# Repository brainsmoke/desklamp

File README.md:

# desk lamp

An attempt to try to build something, mostly from materials I already had on hand.

White LED lamp made with aluminium PCBs

|  |  |
|-|-|
|  |  |

# Serial commands (115200 baud)

```
$ screen /dev/ttyUSB1 115200

lampsh> help
commands:

blink
debug
factory reset
help
load blink [fade {0.00-60.00}]
load calibrations
load custom {0..3} [fade {0.00-60.00}]
load default [fade {0.00-60.00}]
off [fade {0.00-60.00}]
on [fade {0.00-60.00}]
print
reset
restore blink
restore calibrations
restore custom {0..3}
restore default
save blink
save calibrations
save custom {0..3}
save default
set gamma {1.0-5.5}
set led {0..8} ({0.00-100.00} | dial{0,1,2}[:{0.00-100.00}]) [fade {0.00-60.00}]
set leds ({0.00-100.00} | dial{0,1,2}[:{0.00-100.00}]) x 9 [fade {0.00-60.00}]
set max brightness {0.00-100.00}

```

## examples

```
lampsh> set max brightness 50.00               # set maximum brightness to 50%
lampsh> save                                   # make it permanent by saving it to eeprom
```

```
lampsh> set led 2 dial2:50.00                  # use dial2 to dim led 2 in the range 0%-50%

lampsh> set leds dial0 0 0 0 dial1 0 0 0 dial2 # drive one led/dial, each a different temp & pcb

lampsh> set leds dial0 dial1 dial2 dial0 dial1 dial2 dial0 dial1 dial2 # default setting
```

# Firmware

```
apt install avr-gcc gmake pip3
pip3 install pymcuprog
cd firmware/attiny1624
make
make flash

```

# LED brightness calculation

```

    per LED                                      interpolate       apply     scale
     config                                      transition        gamma   brightness
 --------------                                 -------------     -------  ----------
                                                                              max 
 current config                                t_cur / interval    gamma   brightness
                                                     |               |         |
 .-------------.                                     V               V         |
 | per LED     |               .---.         .---------------.  .--------.     |
 | brightness  |---------------- * --------->|          .__  |  |        |     V
 |_____________|               '-^-'         |        ."     |  |       '|   .---.
                                 |           |       /       |->|      / |-->| * |
 .-------------.           .------------. .->|      /        |  |     /  |   '---'
 | per LED     |-dial 0-2->| dial value | |  |  __-'         |  | __-'   |     |
 | dial select |           |------------| |  '_______________'  '________'     |
 |_____________|-no dial-->| max        | |  |               |                 V
                           |____________| |  | sigmoid       |          .------------.
 previous config                          |  | interpolation |          |    LED     |
                                          |  |_______________|          | brightness |
 .-------------.                          |                             '------------'
 | per LED     |               .---.      |
 | brightness  |---------------- * -------'
 |_____________|               '-^-'
                                 |
 .-------------.           .------------.
 | per LED     |-dial 0-2->| dial value |
 | dial select |           |------------|
 |_____________|-no dial-->| max        |
                           |____________|
                           
```

# LED PCBs are leftovers from:

https://github.com/brainsmoke/aluball

## PADAUK software:

https://github.com/brainsmoke/softpwmpdk

`./write.sh <address>` for each in 0..2

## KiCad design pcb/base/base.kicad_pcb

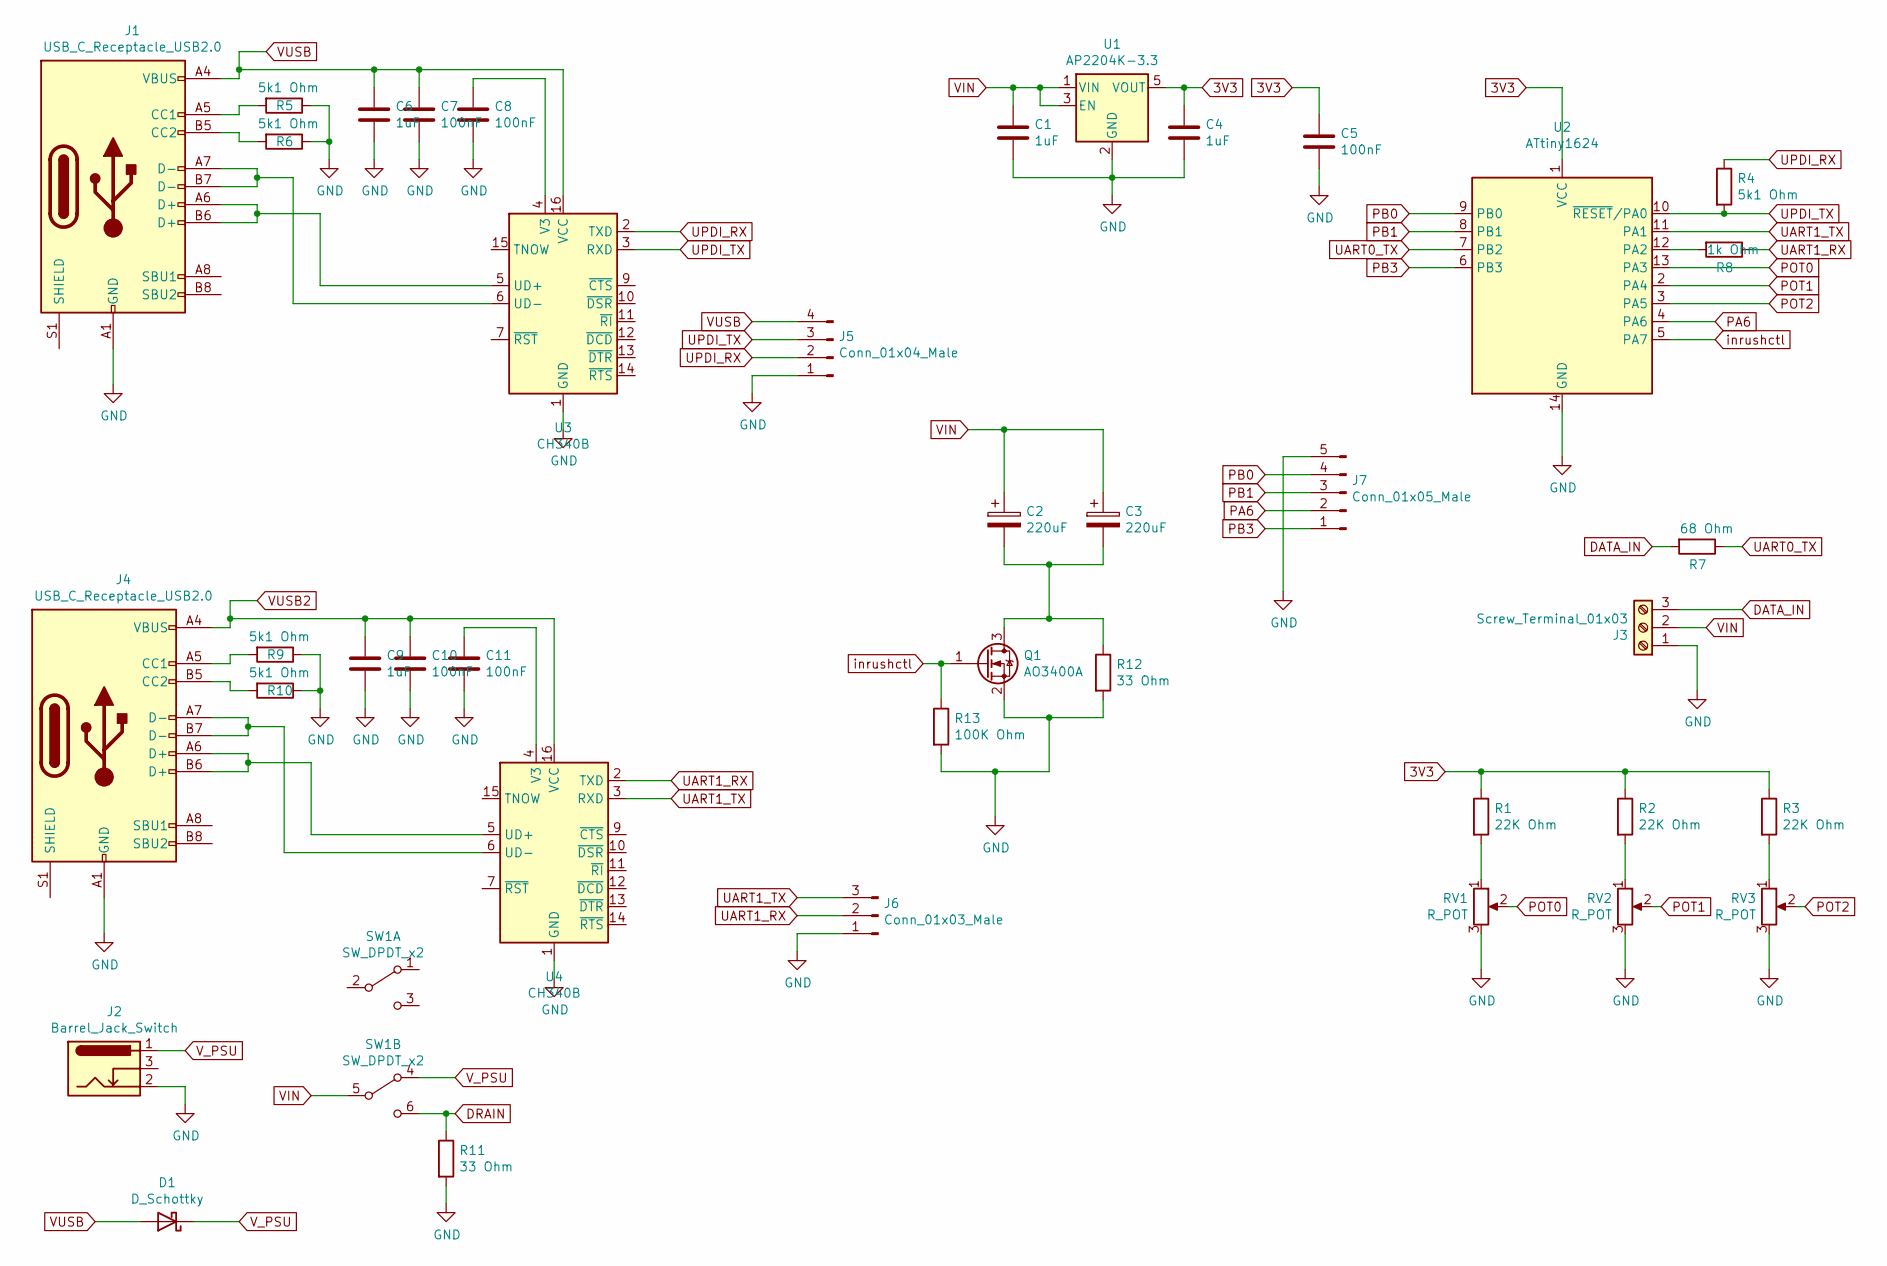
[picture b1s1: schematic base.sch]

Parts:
C1, C4, C6, C9: 1uF; C_0603_1608Metric_Pad1.08x0.95mm_HandSolder
C2, C3: 220uF; CP_Elec_10x10
C5, C7, C8, C10, C11: 100nF; C_0603_1608Metric_Pad1.08x0.95mm_HandSolder
D1: D_Schottky; D_SOD-123
J1, J4: USB_C_Receptacle_USB2.0; USB_C_Receptacle_HRO_TYPE-C-31-M-12
J2: Barrel_Jack_Switch; BarrelJack_Horizontal
J3: Screw_Terminal_01x03; TerminalBlock_Phoenix_PT-1,5-3-5.0-H_1x03_P5.00mm_Horizontal
J5: Conn_01x04_Male; PinHeader_1x04_P2.54mm_Vertical
J6: Conn_01x03_Male; PinHeader_1x03_P2.54mm_Vertical
J7: Conn_01x05_Male; PinHeader_1x05_P2.54mm_Vertical
Q1: AO3400A; SOT-23
R1, R2, R3: 22K Ohm; R_0603_1608Metric_Pad0.98x0.95mm_HandSolder
R4, R5, R6, R9, R10: 5k1 Ohm; R_0603_1608Metric_Pad0.98x0.95mm_HandSolder
R7: 68 Ohm; R_0603_1608Metric_Pad0.98x0.95mm_HandSolder
R8: 1k Ohm; R_0603_1608Metric_Pad0.98x0.95mm_HandSolder
R11, R12: 33 Ohm; R_1206_3216Metric_Pad1.30x1.75mm_HandSolder
R13: 100K Ohm; R_0603_1608Metric_Pad0.98x0.95mm_HandSolder
RV1, RV2, RV3: R_POT; Potentiometer_Alps_RK09L_Single_Vertical_radial
SW1: SW_DPDT_x2; MTS-20X_DPDT
U1: AP2204K-3.3; SOT-23-5
U2: ATtiny1624; SOIC-14_3.9x8.7mm_P1.27mm
U3, U4: CH340B; SOIC-16_3.9x9.9mm_P1.27mm

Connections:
3V3: C4.1, C5.1, R1.1, R2.1, R3.1, U1.5 (VOUT), U2.1 (VCC)
DATA_IN: J3.3, R7.2
DRAIN: R11.1, SW1.6 (C)
GND: C1.2, C4.2, C5.2, C6.2, C7.2, C8.2, C9.2, C10.2, C11.2, J1.A1 (GND), J1.A12 (GND), J1.B1 (GND), J1.B12 (GND), J2.2, J3.1, J4.A1 (GND), J4.A12 (GND), J4.B1 (GND), J4.B12 (GND), J5.1, J6.1, J7.5, Q1.2 (S), R5.1, R6.1, R9.1, R10.1, R11.2, R12.2, R13.2, RV1.3, RV2.3, RV3.3, U1.2 (GND), U2.14 (GND), U3.1 (GND), U4.1 (GND)
unnamed: C2.2, C3.2, Q1.3 (D), R12.1
unnamed: C8.1, U3.4 (V3)
unnamed: C11.1, U4.4 (V3)
unnamed: J1.A5 (CC1), R5.2
unnamed: J1.A6 (D+), J1.B6 (D+), U3.5 (UD+)
unnamed: J1.A7 (D-), J1.B7 (D-), U3.6 (UD-)
unnamed: J1.B5 (CC2), R6.2
unnamed: J4.A5 (CC1), R9.2
unnamed: J4.A6 (D+), J4.B6 (D+), U4.5 (UD+)
unnamed: J4.A7 (D-), J4.B7 (D-), U4.6 (UD-)
unnamed: J4.B5 (CC2), R10.2
unnamed: R1.2, RV1.1
unnamed: R2.2, RV2.1
unnamed: R3.2, RV3.1
unnamed: R8.2, U2.12 (PA2)
PA6: J7.2, U2.4 (PA6)
PB0: J7.4, U2.9 (PB0)
PB1: J7.3, U2.8 (PB1)
PB3: J7.1, U2.6 (PB3)
POT0: RV1.2, U2.13 (PA3)
POT1: RV2.2, U2.2 (PA4)
POT2: RV3.2, U2.3 (PA5)
UART0_TX: R7.1, U2.7 (PB2)
UART1_RX: J6.2, R8.1, U4.2 (TXD)
UART1_TX: J6.3, U2.11 (PA1), U4.3 (RXD)
UPDI_RX: J5.2, R4.1, U3.2 (TXD)
UPDI_TX: J5.3, R4.2, U2.10 (~RESET~/PA0), U3.3 (RXD)
VIN: C1.1, C2.1, C3.1, J3.2, SW1.5 (B), U1.1 (VIN), U1.3 (EN)
VUSB: C6.1, C7.1, D1.2 (A), J1.A4 (VBUS), J1.A9 (VBUS), J1.B4 (VBUS), J1.B9 (VBUS), J5.4, U3.16 (VCC)
VUSB2: C9.1, C10.1, J4.A4 (VBUS), J4.A9 (VBUS), J4.B4 (VBUS), J4.B9 (VBUS), U4.16 (VCC)
V_PSU: D1.1 (K), J2.1, SW1.4 (A)
inrushctl: Q1.1 (G), R13.1, U2.5 (PA7)

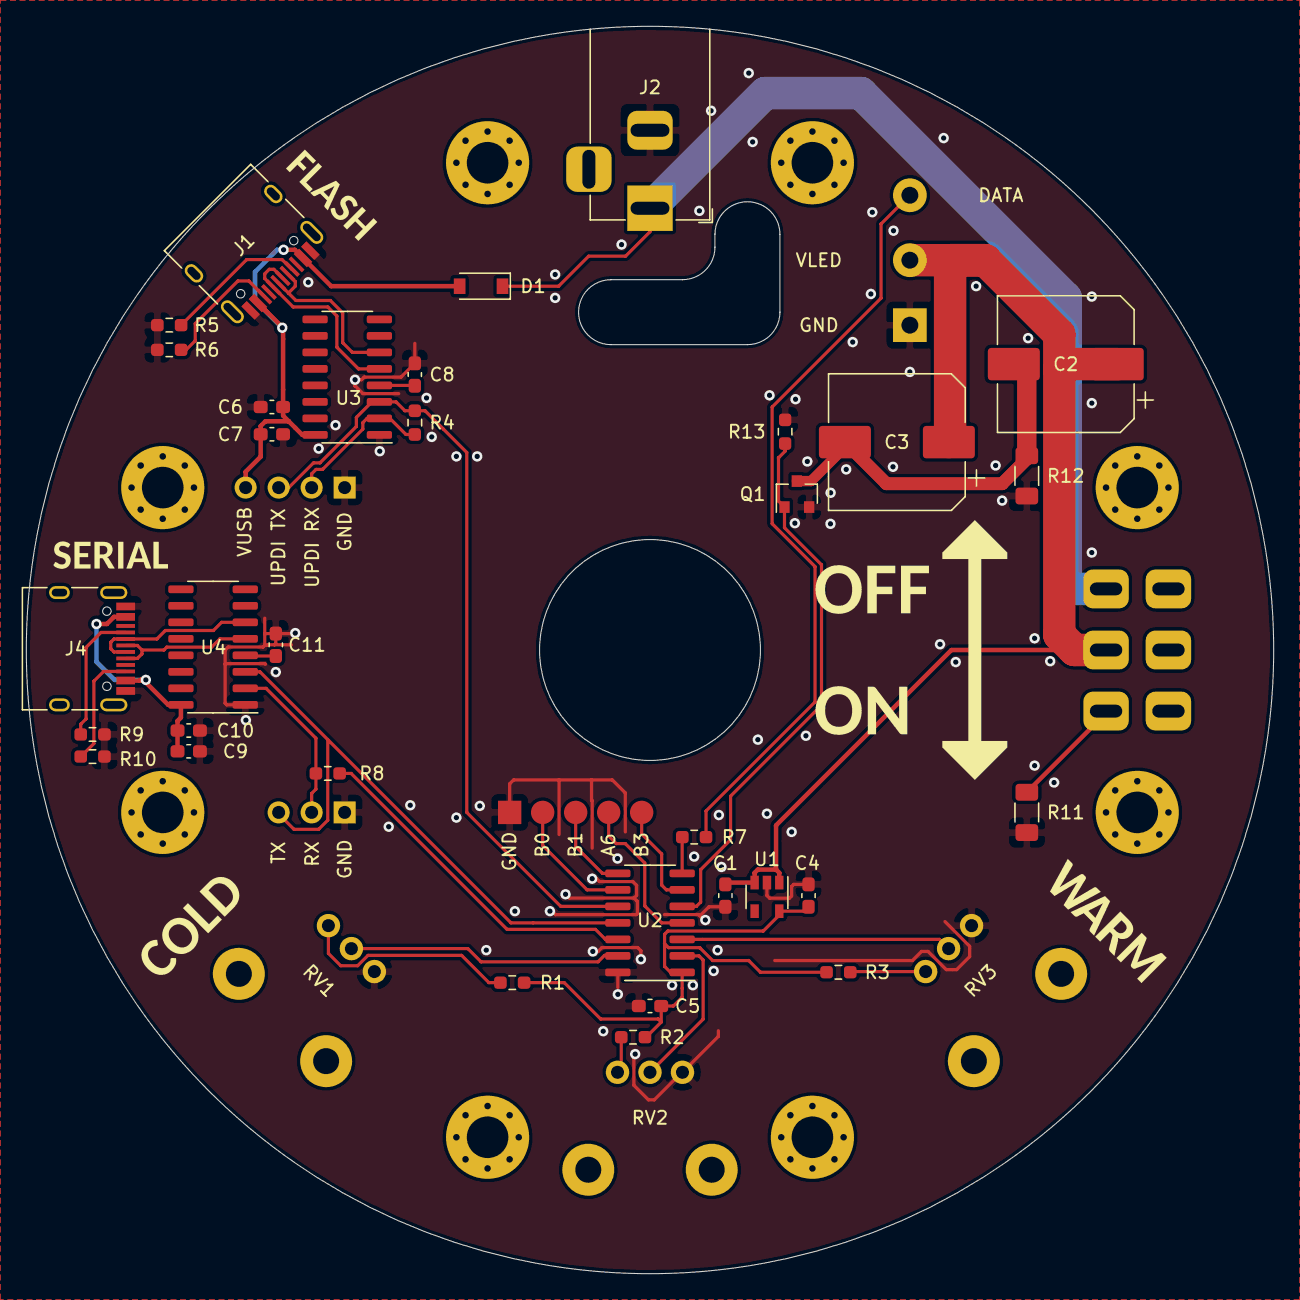
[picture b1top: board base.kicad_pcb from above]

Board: 2 copper layers, 96.0 x 96.0 mm, 41 parts (0 on the bottom side), 36 nets.

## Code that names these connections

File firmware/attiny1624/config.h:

#ifndef CONFIG_H
#define CONFIG_H

#define F_CPU 10000000UL
#define F_CPU_BITS (CLKCTRL_PEN_bm) /* has to match with the bits for F_CPU */

#define EEPROM_MAGIC (0x504d414c)

#define N_DIALS       3
#define DIAL_WHITE             0
#define DIAL_WARM_WHITE        1
#define DIAL_EXTRA_WARM_WHITE  2
#define NO_DIAL                3
#define STR_DIAL_RANGE        "dial{0,1,2}"


#define N_LEDS         9
#define STR_N_LEDS    "9"
#define STR_LED_RANGE "{0..8}"

#define STR_BRIGHTNESS_RANGE "{0.00-100.00}"

#define DEFAULT_FADE (60)
#define STR_FADE_RANGE "{0.00-60.00}"
#define FADE_MAX (6000)

#define STR_GAMMA_RANGE "{1.0-5.5}"

#define LED_ALL_OFF 0,0,0, 0,0,0, 0,0,0
#define LED_ALL_MAX 0xffff, 0xffff, 0xffff, 0xffff, 0xffff, 0xffff, 0xffff, 0xffff, 0xffff

#define LED_BLINK 0xffff, 0, 0, 0xffff, 0, 0, 0xffff, 0, 0

#define LED_ORDER DIAL_WHITE, DIAL_WARM_WHITE, DIAL_EXTRA_WARM_WHITE

#define LED_DIAL_MAP       LED_ORDER, LED_ORDER, LED_ORDER
#define LED_NO_DIAL_MAP NO_DIAL,NO_DIAL,NO_DIAL, NO_DIAL,NO_DIAL,NO_DIAL, NO_DIAL,NO_DIAL,NO_DIAL

#define LED_UART_RESHUFFLE 0,2,1,3,5,4,6,8,7

#define ANIMATION_QUEUE_SIZE 16

#define N_CUSTOM            4
#define N_PRESETS           6
#define PRESET_CUSTOM_BASE  0
#define PRESET_DEFAULT      4
#define PRESET_BLINK        5
#define STR_CUSTOM_RANGE "{0..3}"
#define PRESET_NAMES "custom 0", "custom 1", "custom 2", "custom 3", "default", "blink"

#define DIAL_MIN_DEFAULT 600
#define DIAL_MAX_DEFAULT 60000
#define DIAL_DEADZONE 400        /* full-on / full-off regions */

#define DEFAULT_MAX_BRIGHTNESS (65535)
#define DEFAULT_GAMMA_DEC (20) /* gamma = gamma_dec/10 */

#define ADC_PIN_0     3
#define ADC_PORT_0    PORTA
#define ADC_PINCTRL_0 PORTA.PIN3CTRL
#define ADC_AIN_0     3

#define ADC_PIN_1     4
#define ADC_PORT_1    PORTA
#define ADC_PINCTRL_1 PORTA.PIN4CTRL
#define ADC_AIN_1     4

#define ADC_PIN_2     5
#define ADC_PORT_2    PORTA
#define ADC_PINCTRL_2 PORTA.PIN5CTRL
#define ADC_AIN_2     5

#define USART0_BAUDRATE 38400
#define USART1_BAUDRATE 115200

#define USART0_RX_BUF_SZ (1)
#define USART1_RX_BUF_SZ (254)


#define USART0_PORTMUX PORTMUX_USART0_DEFAULT_gc // RX = PB3, TX = PB2
#define USART0_BAUD_REG ( (F_CPU*64 + 8ul*USART0_BAUDRATE)/(16ul*USART0_BAUDRATE) )

#define USART1_PORTMUX PORTMUX_USART1_DEFAULT_gc // RX = PA2, TX = PA1
#define USART1_BAUD_REG ( (F_CPU*64 + 8ul*USART1_BAUDRATE)/(16ul*USART1_BAUDRATE) )

#define USART0_RX_PIN 3
#define USART0_RX_PORT PORTB
#define USART0_RX_PINCTRL PORTB.PIN3CTRL

#define USART0_TX_PIN 2
#define USART0_TX_PORT PORTB
#define USART0_TX_PINCTRL PORTB.PIN2CTRL

#define USART1_RX_PIN 2
#define USART1_RX_PORT PORTA
#define USART1_RX_PINCTRL PORTA.PIN2CTRL

#define USART1_TX_PIN 1
#define USART1_TX_PORT PORTA
#define USART1_TX_PINCTRL PORTA.PIN1CTRL

#endif //CONFIG_H

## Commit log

2023-04-08 pcb ok, code untested
2023-04-08 debug some stuff
2023-04-09 add gamma config
2023-04-09 fix dial to colour mapping
2023-04-10 remove inv parameter in output
2023-04-10 add rtc leap calculator
2023-04-13 use yield() for polling
2023-04-14 readme
2023-04-14 add smooth transitions
2023-04-14 add PCB image
2023-04-15 copy animation presets by value in animation queue
2023-04-15 add led preset config parser function
2023-04-15 allow setting leds over serial
2023-04-15 rename dial[1..3] to dial[0..2] for consistency
2023-04-15 well.. oops
2023-04-15 improve command parsing, add help command
2023-04-15 add commands to readme
2023-04-16 wut!?
2023-04-16 fix crlf handling
2023-04-16 use percentages for brightness
2023-04-16 clarify documentation
2023-04-16 firmware build doc
2023-04-17 optimise interpolation stuff
2023-04-18 save the bytes! reuse code
2023-04-18 rename config => dial member in preset_t
2023-04-18 add drain resistor to pcb
2023-04-18 rename preset_t to ledconfig_t
2023-04-19 add configurable presets
2023-04-19 add uart header
2023-04-19 remove unused header
2023-04-19 change {load,save} commands to {load,save,restore} calibrations
2023-04-19 simplefy code
2023-04-19 fix arg parsing
2023-04-20 add print command
2023-04-20 add print command to readme
2023-04-21 add drain resistor to the switch's off side
2023-04-22 document led brightness calculation
2023-04-22 remove unused caps
2023-04-23 tweak readme
2023-04-28 inrush current limitter
2023-04-29 update build instructions
2023-04-29 improve readme
2023-04-30 readme edit
2023-04-30 add SMD pads for unused pins because why not
2023-06-11 add fade commands
2023-06-12 set brownout fuse
2023-06-12 update PCB
2023-06-27 limit fade to a max of 60 seconds
2023-07-22 change fade commands
2023-09-02 fix on/off commands... oopsie
2023-09-02 improve help
2024-01-12 fix "save blink"
